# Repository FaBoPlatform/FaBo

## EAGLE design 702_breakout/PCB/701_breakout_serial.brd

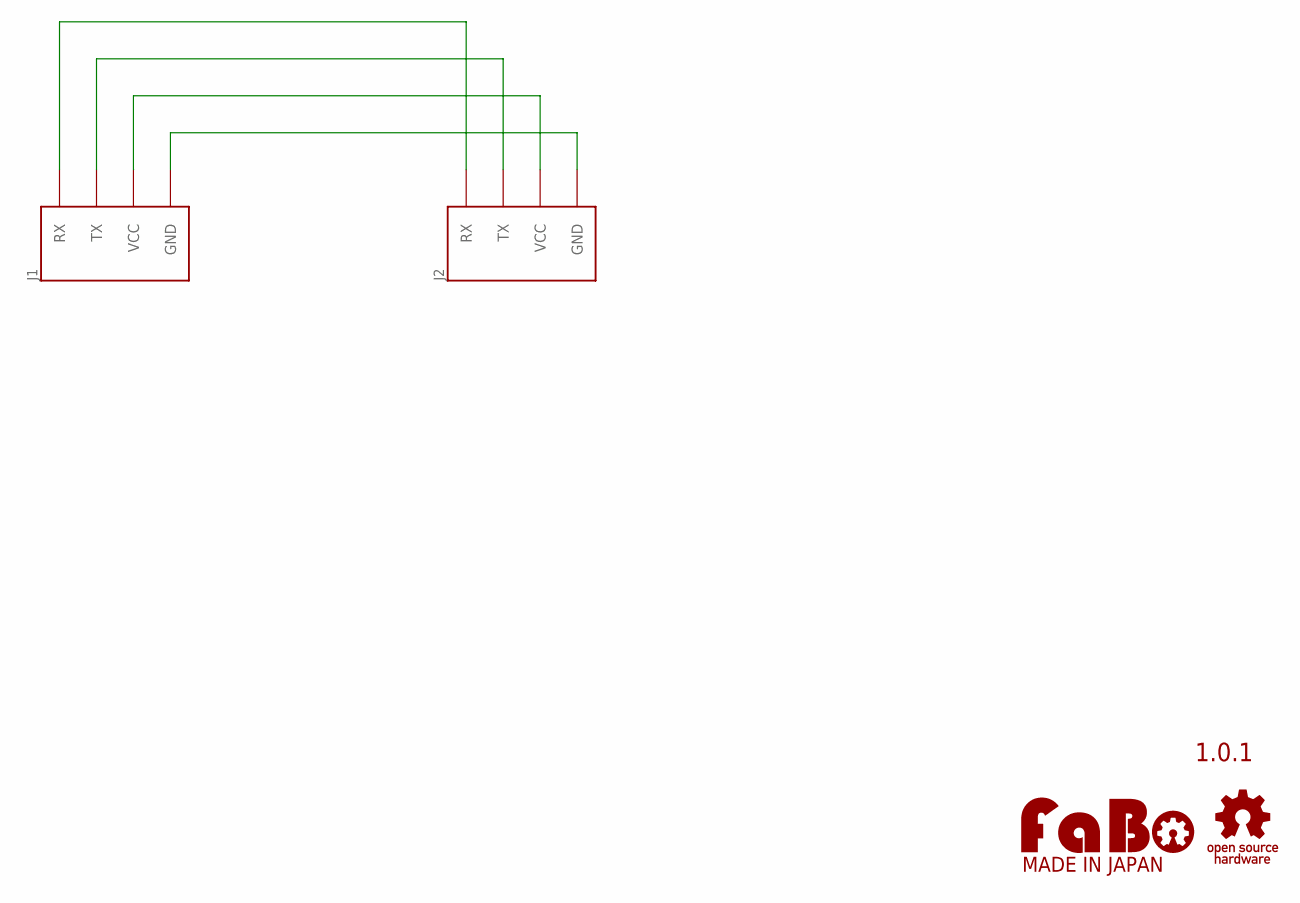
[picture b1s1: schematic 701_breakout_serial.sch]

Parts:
J1: FABO_BRICK_SERIAL-BREAKOUT; FABO_BRICK_SERIAL_BREAKOUT
J2: FABO_BRICK_SERIAL-CONNECTOR; FABO_BRICK_SERIAL_CONNECTOR
U$2: LOGO_FABO-M_BOTTOM; LOGO_FABO_MS_BOTTOM
U$3: LOGO_OSHW-S_BOTTOM; LOGO_OSHW_S_BOTTOM

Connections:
GND: J1.GND, J2.GND
SCL: J1.RX, J2.RX
SDA: J1.TX, J2.TX
VCC: J1.VCC, J2.VCC

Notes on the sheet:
1.0.1

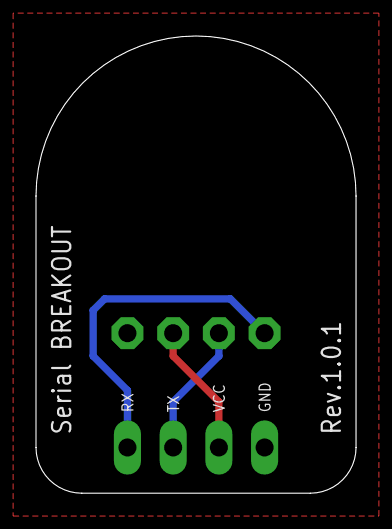
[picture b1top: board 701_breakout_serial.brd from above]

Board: 2 copper layers, 17.8 x 25.4 mm, 4 parts (0 on the bottom side), 4 nets.

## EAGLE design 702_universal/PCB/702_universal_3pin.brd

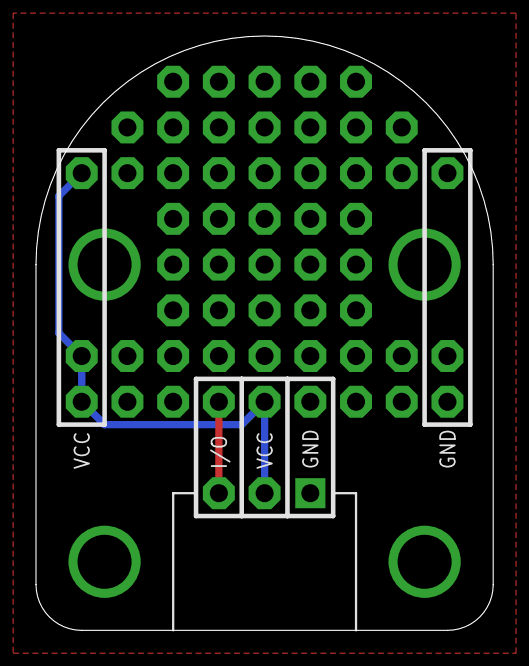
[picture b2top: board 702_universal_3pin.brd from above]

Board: 2 copper layers, 25.4 x 33.0 mm, 12 parts (0 on the bottom side), 3 nets.

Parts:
J1: FABO_BRICK_3PIN_UNIVERSAL
J2, J3, J4, J5, J6, J7, J8, J9, J10: PIN_1X1_NONAME
U$1: LOGO_OSHW_S_BOTTOM
U$3: LOGO_FABO_M_BOTTOM

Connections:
GND: J1.GND, J7.1, J8.1, J9.1, J10.1
IO: J1.IN/OUT, J2.1
VCC: J1.VCC, J3.1, J4.1, J5.1, J6.1

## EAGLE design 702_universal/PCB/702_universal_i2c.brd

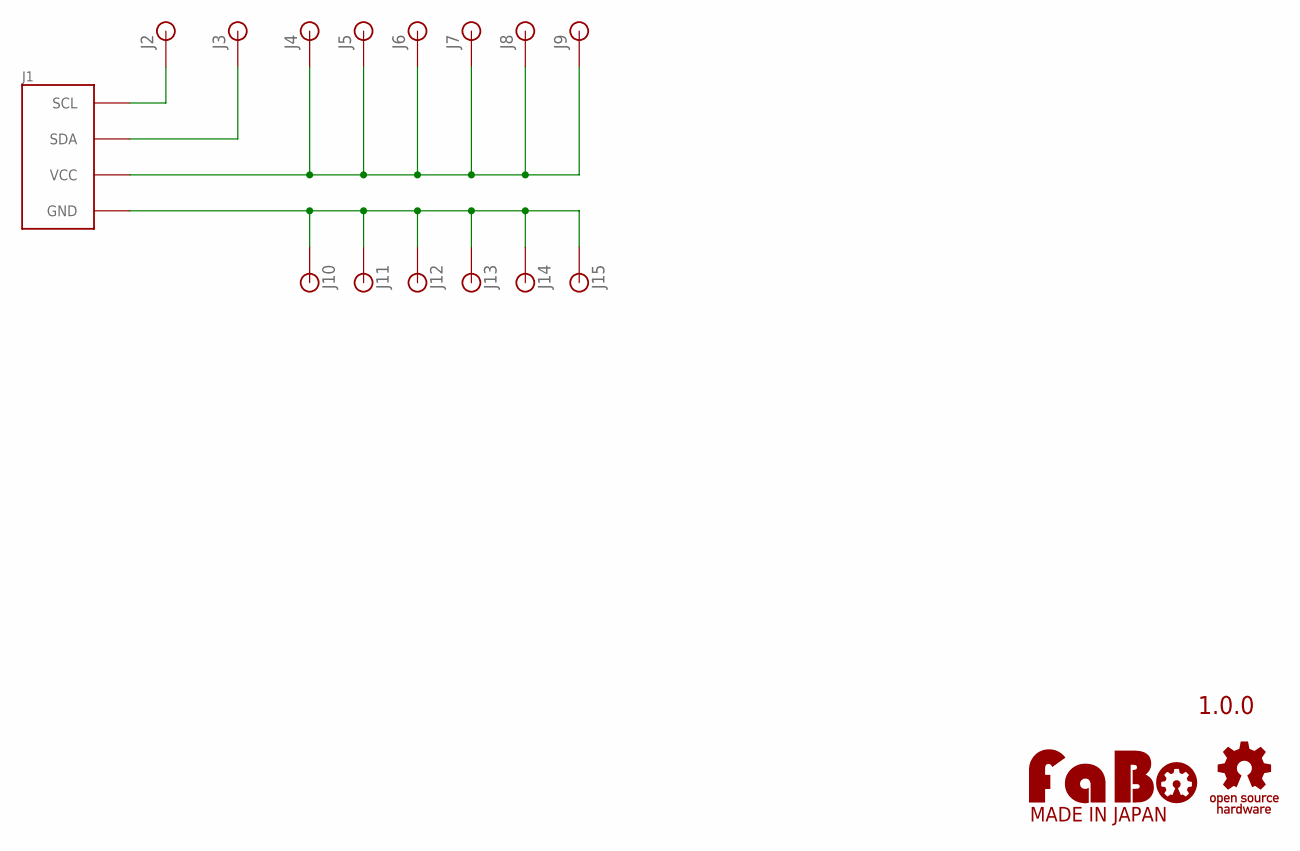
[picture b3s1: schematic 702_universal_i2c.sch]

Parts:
J1: FABO_BRICK_I2C-UNIVERSAL; FABO_BRICK_I2C_UNIVERSAL
J2, J3, J4, J5, J6, J7, J8, J9, J10, J11, J12, J13, J14, J15: PINHEAD_1X1-NONAME; PIN_1X1_NONAME
U$16: LOGO_OSHW-S_BOTTOM; LOGO_OSHW_S_BOTTOM
U$17: LOGO_FABO-M_BOTTOM; LOGO_FABO_M_BOTTOM

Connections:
GND: J1.GND, J10.1, J11.1, J12.1, J13.1, J14.1, J15.1
SCL: J1.SCL, J2.1
SDA: J1.SDA, J3.1
VCC: J1.VCC, J4.1, J5.1, J6.1, J7.1, J8.1, J9.1

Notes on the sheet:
1.0.0

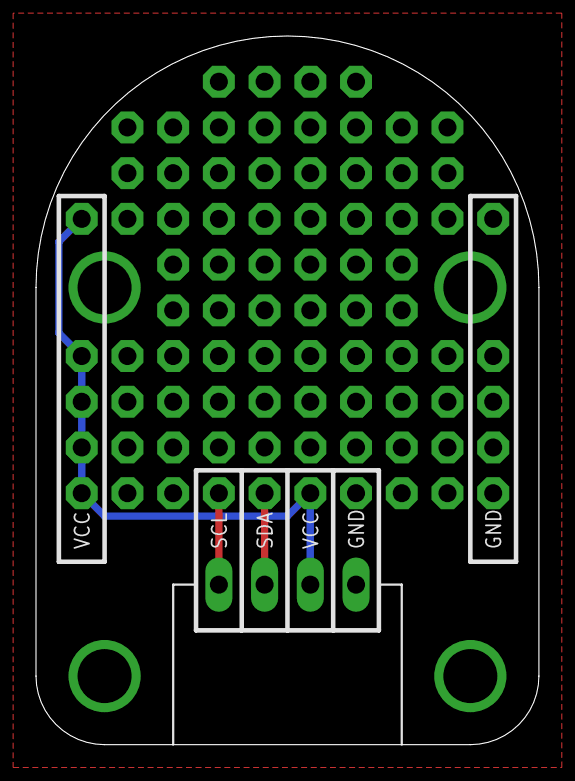
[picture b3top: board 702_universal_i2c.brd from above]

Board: 2 copper layers, 27.9 x 39.4 mm, 17 parts (0 on the bottom side), 4 nets.

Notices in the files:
parts and their libraries:
FaBo-etc: Released under the Creative Commons Attribution-ShareAlike 4.0 License
https://creativecommons.org/licenses/by-sa/4.0
FaBo-etc: Released under the Creative Commons
